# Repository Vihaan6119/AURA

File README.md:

# AURA 

AURA is a custom mechanical desktop controller designed for media navigation and other things basic need in my life. It is built around a Raspberry Pi Pico, it has 6 mechanical keys, an 0.91 inch OLED display, and a multi-function rotary knob.

In simple words, I have made a PCB which has the neccessary areas and cutout (inside the PCB) to solder the parts in. 

Here the Rasberry Pi Pico works as the main controller of this project which handels all the working from presseng the switches, turning the knob to the text in the display. It controls almost everything. 

For the controls I have used the Key which will help me do a the kind of shortcut which i like to have on it. 

The knob is there for the up/down scrolling and the left/right scrolling in PDFs, webpages, CAD apps, 3D modeling, volume control, etc. 

The display is for showing wither the time or the current sony which is being play, with basic info in it. (this can also be coustomised from the firmware of the project).

I have specially designed a coustom enclosure for this, which is in 2 parts.

Base part:
    Here is where the PCB will be sitting. It will be mounted securly by the M3 mounting holes. There is a cutout on the back side of the Base so that we can connect the power/data cable to the Rasberry Pi Pico. 

Top Lid:
    The lid will be placed on the base lid securly. There are required cutouts for the display, the keys and the knob. 

I have made the colour of base as the default color, and the top in orange color to differential between them and make it easier for me to make and assemble the full enclosure with the PCB and all the parts. 
In the final printing, the enclosure will have a black colour (from the black PLA filament from the printing legion).

## Instructions AURA enclosure files

The .step file of the PCB is in the folder named**Hardware**. The name of the exact file is **AURA V2.step**
The rest of the file are in the folder named **Enclosure**.

The base part is of the name **AURA base.step**. 
The top Lid is of the name **AURA lid.step**.
The complete assembly of the enclosure with the PCB is of the name **AURA Full Assembly.step**.

## INSTRUCTIONS TO FOLLOW TO GET THE THE ASSEMBLED .STEP FILE

Unfortunatily, there is a specify way in which you have to open the **AURA Full Assembly.step** to actully get the the fully assembled file which has the base, top lid and the PCB with all the parts. 

This is the way (for this I am using Onshape. I think it will almost similar for all the different softwares):

* **uploading the file:** Click import (wherever the option is in your software) and select the specific file named **AURA Full Assembly.step**
* It will take 1-2 mins in importing all the parts. 
* **Selecting the file:** After all the parts are successfully imported, from all the different files, you have to select the one which is named **AURA V2 1**. This is the file which will contain the fully assembled file.

---
## Key Features

* **Microcontroller:** Powered by the Raspberry Pi Pico (RP2040).
* **Macro Matrix:** 6 mechanical keys (`SW2` through `SW7`).
* **Interactive OLED Display:** A 0.91-inch SSD1306.
* **Multi-Function Rotary Encoder (The Crown):** 
  * *Default:* Vertical scrolling.
  * *Shift + Rotate:* Horizontal scrubbing / zooming.
  * *Fn + Rotate:* System volume control.
  * *Push Switch:* Quick action trigger.
* **Smart Power-Saving:** Automatic 15-minute inactivity sleep timer to preserve screen life.
* **Dynamic Configuration:** Easily remap keys without rewriting firmware by editing a simple `config.json` file stored directly on the device.
* **Secure Enclosure Ready:** Integrated corner M3 mounting holes (`H1`–`H4`) for robust case assembly.
---

| Item | Qty | Supplier | Cost/item | Total Cost | Link |
| :--- | :---: | :--- | ---: | ---: | :--- |
| Raspberry Pi Pico | 1 | besomi | $8.00 | $8.00 | [Link](https://besomi.com/ae_en/) |
| SSD1306 OLED Display (0.91") | 1 | AliExpress | $1.23 | $1.23 | [Link](https://ar.aliexpress.com/?gatewayAdapt=glo2ara) |
| EC11 Rotary Encoder with Switch | 1 | LCSC | $2.22 | $2.22 | [Link](https://www.lcsc.com/) |
| Cherry MX Mechanical Switches | 10 | AliExpress | $0.71 | $7.10 | [Link](https://ar.aliexpress.com/?gatewayAdapt=glo2ara) |
| M3 Screws and Standoffs Set | 30 | ALiExpress | $0.12 | $3.60 | [Link](https://ar.aliexpress.com/?gatewayAdapt=glo2ara) |
| Custom PCB (AURA) | 5 | JLC PCB | $0.80 | $4.00 | [Link](https://jlcpcb.com/) |
| Estimated total shipping | 1 | Printing Legion | $3.00 | $3.00 | [Link](https://printlegion.hackclub.com/) |

**Tax & shipping:** $15.59  
**Total:** $44.75

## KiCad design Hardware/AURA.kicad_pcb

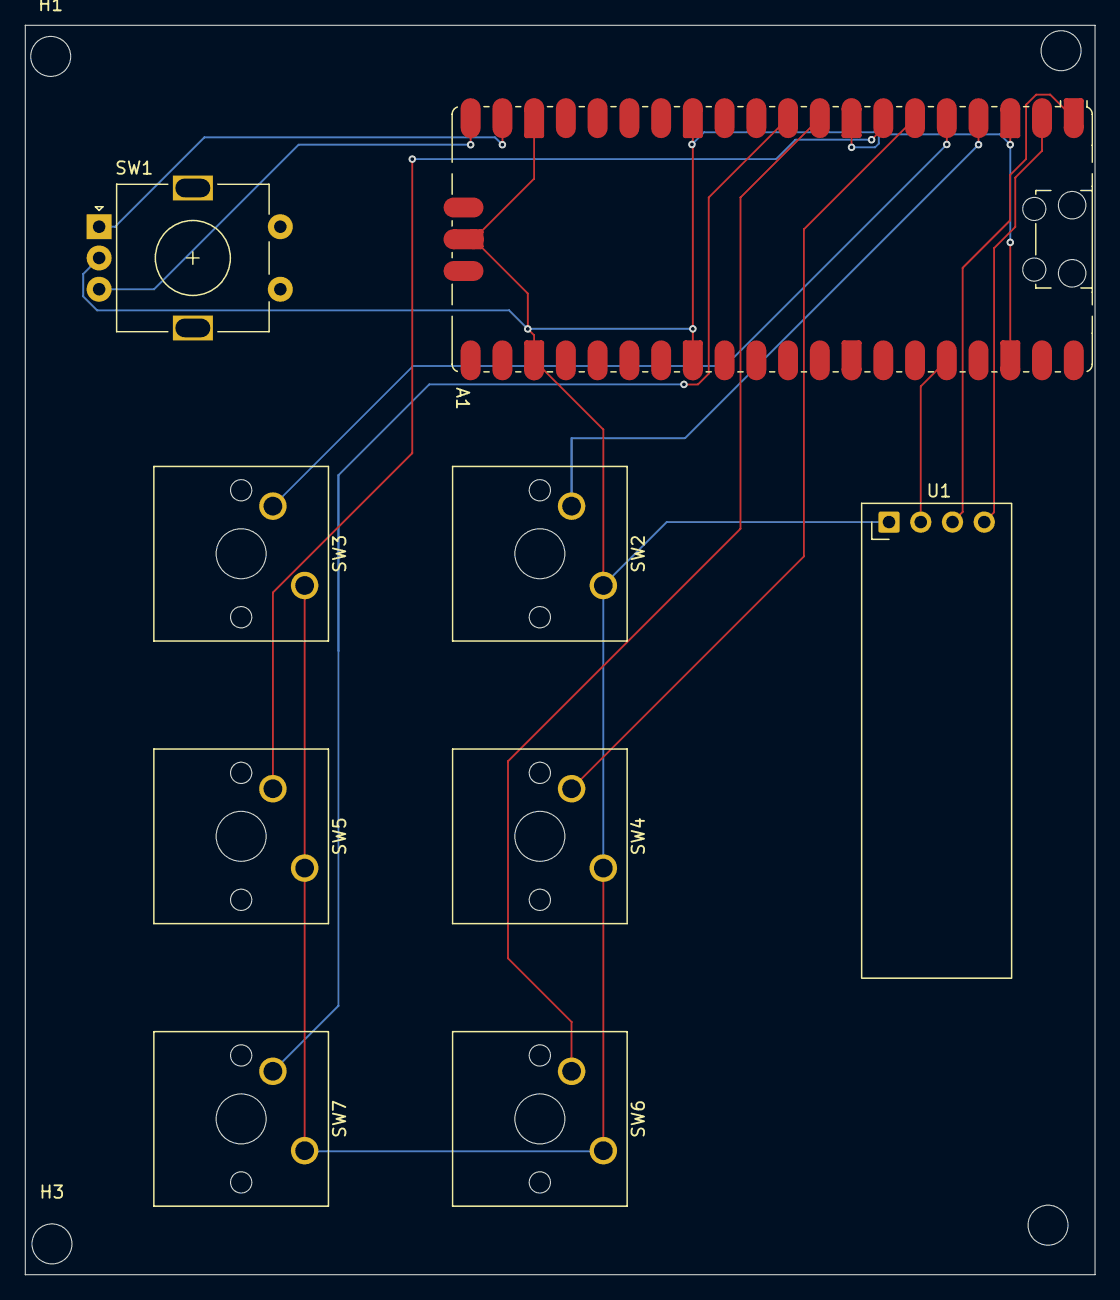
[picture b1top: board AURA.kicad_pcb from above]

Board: 2 copper layers, 85.6 x 100.0 mm, 13 parts (0 on the bottom side), 12 nets.

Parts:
A1: RaspberryPi_Pico; RaspberryPi_Pico_SMD_HandSolder
H1, H2, H3, H4: MountingHole; MountingHole_3.2mm_M3
SW1: EC11E18244AU; RotaryEncoder_Alps_EC11E-Switch_Vertical_H20mm
SW2, SW3, SW4, SW5, SW6, SW7: SW_Push; SW_Cherry_MX_1.00u_PCB
U1: ER_OLEDM0.91_1x-I2C

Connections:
+3.3V: A1.36 (3V3), U1.2 (VCC)
GND: A1.3 (GND), A1.8 (GND), A1.13 (GND), A1.18 (GND), A1.23 (GND), A1.28 (GND), A1.38 (GND), A1.D2 (GND), SW1.C, SW2.1, SW3.1, SW4.1, SW5.1, SW6.1, SW7.1, U1.1 (GND)
unnamed: A1.1 (GPIO0), U1.3 (SCL)
unnamed: A1.2 (GPIO1), U1.4 (SDA)
unnamed: A1.4 (GPIO2), SW2.2
unnamed: A1.5 (GPIO3), SW3.2
unnamed: A1.6 (GPIO4), SW4.2
unnamed: A1.7 (GPIO5), SW5.2
unnamed: A1.9 (GPIO6), SW6.2
unnamed: A1.10 (GPIO7), SW7.2
unnamed: A1.19 (GPIO14), SW1.A
unnamed: A1.20 (GPIO15), SW1.B
